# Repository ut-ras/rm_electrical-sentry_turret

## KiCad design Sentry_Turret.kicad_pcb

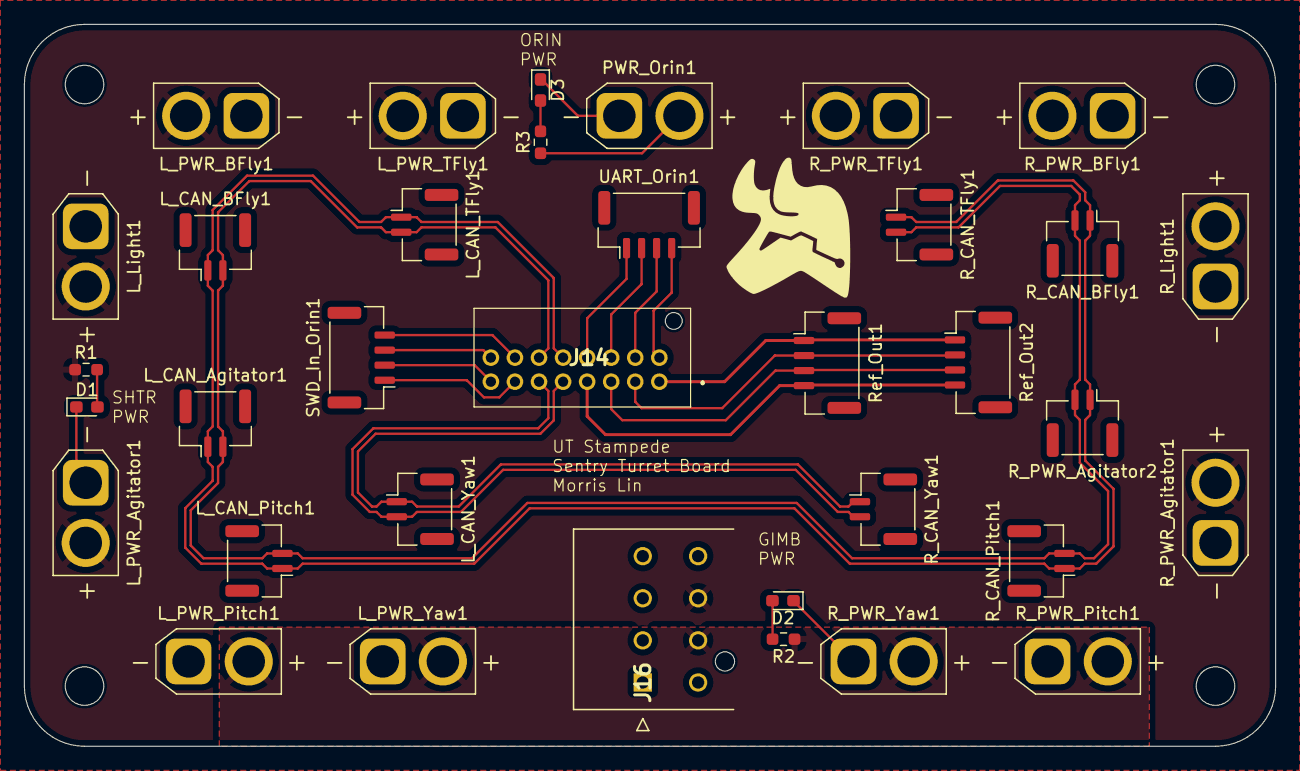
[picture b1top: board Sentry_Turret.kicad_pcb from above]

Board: 2 copper layers, 104.0 x 60.0 mm, 39 parts (0 on the bottom side), 25 nets.

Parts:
D1, D2, D3: 150060YS75000; LED_0603_1608Metric_Pad1.05x0.95mm_HandSolder
H1, H2, H3, H4: MountingHole; MountingHole_3.2mm_M3
J14: 501645-1620; 5016451620
J16: 172298-1108; 172298-YY08
L_CAN_Agitator1: Conn_01x02_Pin; JST_GH_BM02B-GHS-TBT_1x02-1MP_P1.25mm_Vertical
L_CAN_BFly1: Conn_01x02_Pin; JST_GH_BM02B-GHS-TBT_1x02-1MP_P1.25mm_Vertical
L_CAN_Pitch1: Conn_01x02_Pin; JST_GH_BM02B-GHS-TBT_1x02-1MP_P1.25mm_Vertical
L_CAN_TFly1: Conn_01x02_Pin; JST_GH_BM02B-GHS-TBT_1x02-1MP_P1.25mm_Vertical
L_CAN_Yaw1: Conn_01x02_Pin; JST_GH_BM02B-GHS-TBT_1x02-1MP_P1.25mm_Vertical
L_Light1: Conn_01x02_Pin; AMASS_XT30U-F_1x02_P5.0mm_Vertical
L_PWR_Agitator1: Conn_01x02_Pin; AMASS_XT30U-F_1x02_P5.0mm_Vertical
L_PWR_BFly1: Conn_01x02_Pin; AMASS_XT30U-F_1x02_P5.0mm_Vertical
L_PWR_Pitch1: Conn_01x02_Pin; AMASS_XT30U-F_1x02_P5.0mm_Vertical
L_PWR_TFly1: Conn_01x02_Pin; AMASS_XT30U-F_1x02_P5.0mm_Vertical
L_PWR_Yaw1: Conn_01x02_Pin; AMASS_XT30U-F_1x02_P5.0mm_Vertical
PWR_Orin1: Conn_01x02_Pin; AMASS_XT30U-F_1x02_P5.0mm_Vertical
R1, R2, R3: 1k; R_0603_1608Metric_Pad0.98x0.95mm_HandSolder
R_CAN_BFly1: Conn_01x02_Pin; JST_GH_BM02B-GHS-TBT_1x02-1MP_P1.25mm_Vertical
R_CAN_Pitch1: Conn_01x02_Pin; JST_GH_BM02B-GHS-TBT_1x02-1MP_P1.25mm_Vertical
R_CAN_TFly1: Conn_01x02_Pin; JST_GH_BM02B-GHS-TBT_1x02-1MP_P1.25mm_Vertical
R_CAN_Yaw1: Conn_01x02_Pin; JST_GH_BM02B-GHS-TBT_1x02-1MP_P1.25mm_Vertical
R_Light1: Conn_01x02_Pin; AMASS_XT30U-F_1x02_P5.0mm_Vertical
R_PWR_Agitator1: Conn_01x02_Pin; AMASS_XT30U-F_1x02_P5.0mm_Vertical
R_PWR_Agitator2: Conn_01x02_Pin; JST_GH_BM02B-GHS-TBT_1x02-1MP_P1.25mm_Vertical
R_PWR_BFly1: Conn_01x02_Pin; AMASS_XT30U-F_1x02_P5.0mm_Vertical
R_PWR_Pitch1: Conn_01x02_Pin; AMASS_XT30U-F_1x02_P5.0mm_Vertical
R_PWR_TFly1: Conn_01x02_Pin; AMASS_XT30U-F_1x02_P5.0mm_Vertical
R_PWR_Yaw1: Conn_01x02_Pin; AMASS_XT30U-F_1x02_P5.0mm_Vertical
Ref_Out1, Ref_Out2: Conn_01x04_Pin; JST_GH_BM04B-GHS-TBT_1x04-1MP_P1.25mm_Vertical
SWD_In_Orin1: Conn_01x04_Pin; JST_GH_BM04B-GHS-TBT_1x04-1MP_P1.25mm_Vertical
UART_Orin1: Conn_01x04_Pin; JST_GH_BM04B-GHS-TBT_1x04-1MP_P1.25mm_Vertical

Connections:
/CAN1+: J14.11, L_CAN_Yaw1.2, R_CAN_Yaw1.2
/CAN1-: J14.9, L_CAN_Yaw1.1, R_CAN_Yaw1.1
/CAN2+: J14.12, L_CAN_Agitator1.2, L_CAN_BFly1.2, L_CAN_Pitch1.2, L_CAN_TFly1.2, R_CAN_BFly1.2, R_CAN_Pitch1.2, R_CAN_TFly1.2, R_PWR_Agitator2.2
/CAN2-: J14.10, L_CAN_Agitator1.1, L_CAN_BFly1.1, L_CAN_Pitch1.1, L_CAN_TFly1.1, R_CAN_BFly1.1, R_CAN_Pitch1.1, R_CAN_TFly1.1, R_PWR_Agitator2.1
/Gimbal_{+24V}: J16.6, L_PWR_Pitch1.2, L_PWR_Yaw1.2, R2.1, R_PWR_Pitch1.2, R_PWR_Yaw1.2
/Gimbal_{GND}: D2.1 (K), J16.2, L_PWR_Pitch1.1, L_PWR_Yaw1.1, R_PWR_Pitch1.1, R_PWR_Yaw1.1
/OrinPWR_{+19V}: J16.8, PWR_Orin1.2, R3.1
/OrinPWR_{GND}: D3.1 (K), J16.4, PWR_Orin1.1
/Ref_{CAN}+: J14.5, Ref_Out1.3, Ref_Out2.3
/Ref_{CAN}-: J14.3, Ref_Out1.2, Ref_Out2.2
/Ref_{GND}: J14.1, Ref_Out1.1, Ref_Out2.1
/Ref_{PWR}: J14.7, Ref_Out1.4, Ref_Out2.4
/SWD_{3V3}: J14.14, SWD_In_Orin1.4
/SWD_{GND}: J14.13, SWD_In_Orin1.1
/SWD_{SWCLK}: J14.16, SWD_In_Orin1.3
/SWD_{SWDIO}: J14.15, SWD_In_Orin1.2
/Shooter_{+24V}: J16.7, L_Light1.2, L_PWR_Agitator1.2, L_PWR_BFly1.2, L_PWR_TFly1.2, R1.1, R_Light1.2, R_PWR_Agitator1.2, R_PWR_BFly1.2, R_PWR_TFly1.2
/Shooter_{GND}: D1.1 (K), J16.3, L_Light1.1, L_PWR_Agitator1.1, L_PWR_BFly1.1, L_PWR_TFly1.1, R_Light1.1, R_PWR_Agitator1.1, R_PWR_BFly1.1, R_PWR_TFly1.1
/UART_{3V3}: J14.2, UART_Orin1.4
/UART_{GND}: J14.8, UART_Orin1.1
/UART_{RX}: J14.4, UART_Orin1.3
/UART_{TX}: J14.6, UART_Orin1.2
unnamed: D1.2 (A), R1.2
unnamed: D2.2 (A), R2.2
unnamed: D3.2 (A), R3.2

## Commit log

2025-02-07 Created blank project and added kicad lib changes
2025-02-07 Moved dirs
2025-02-15 designed sentry turret board
2025-02-19 Added connector and updated kicad lib
2025-02-22 Added hierarchical labels
2025-03-01 add labels to sentry turret connector
2025-03-21 added project-level library
2025-03-22 Update library to checkout on submodule update
2025-03-22 Update fp/sym tables
2025-06-05 Swapped to copy of standard/hero sch
2025-06-06 Finalized schematic, began layout
2025-06-08 Check for jed
2025-06-09 Layout review
2025-06-09 Finalized board for order
